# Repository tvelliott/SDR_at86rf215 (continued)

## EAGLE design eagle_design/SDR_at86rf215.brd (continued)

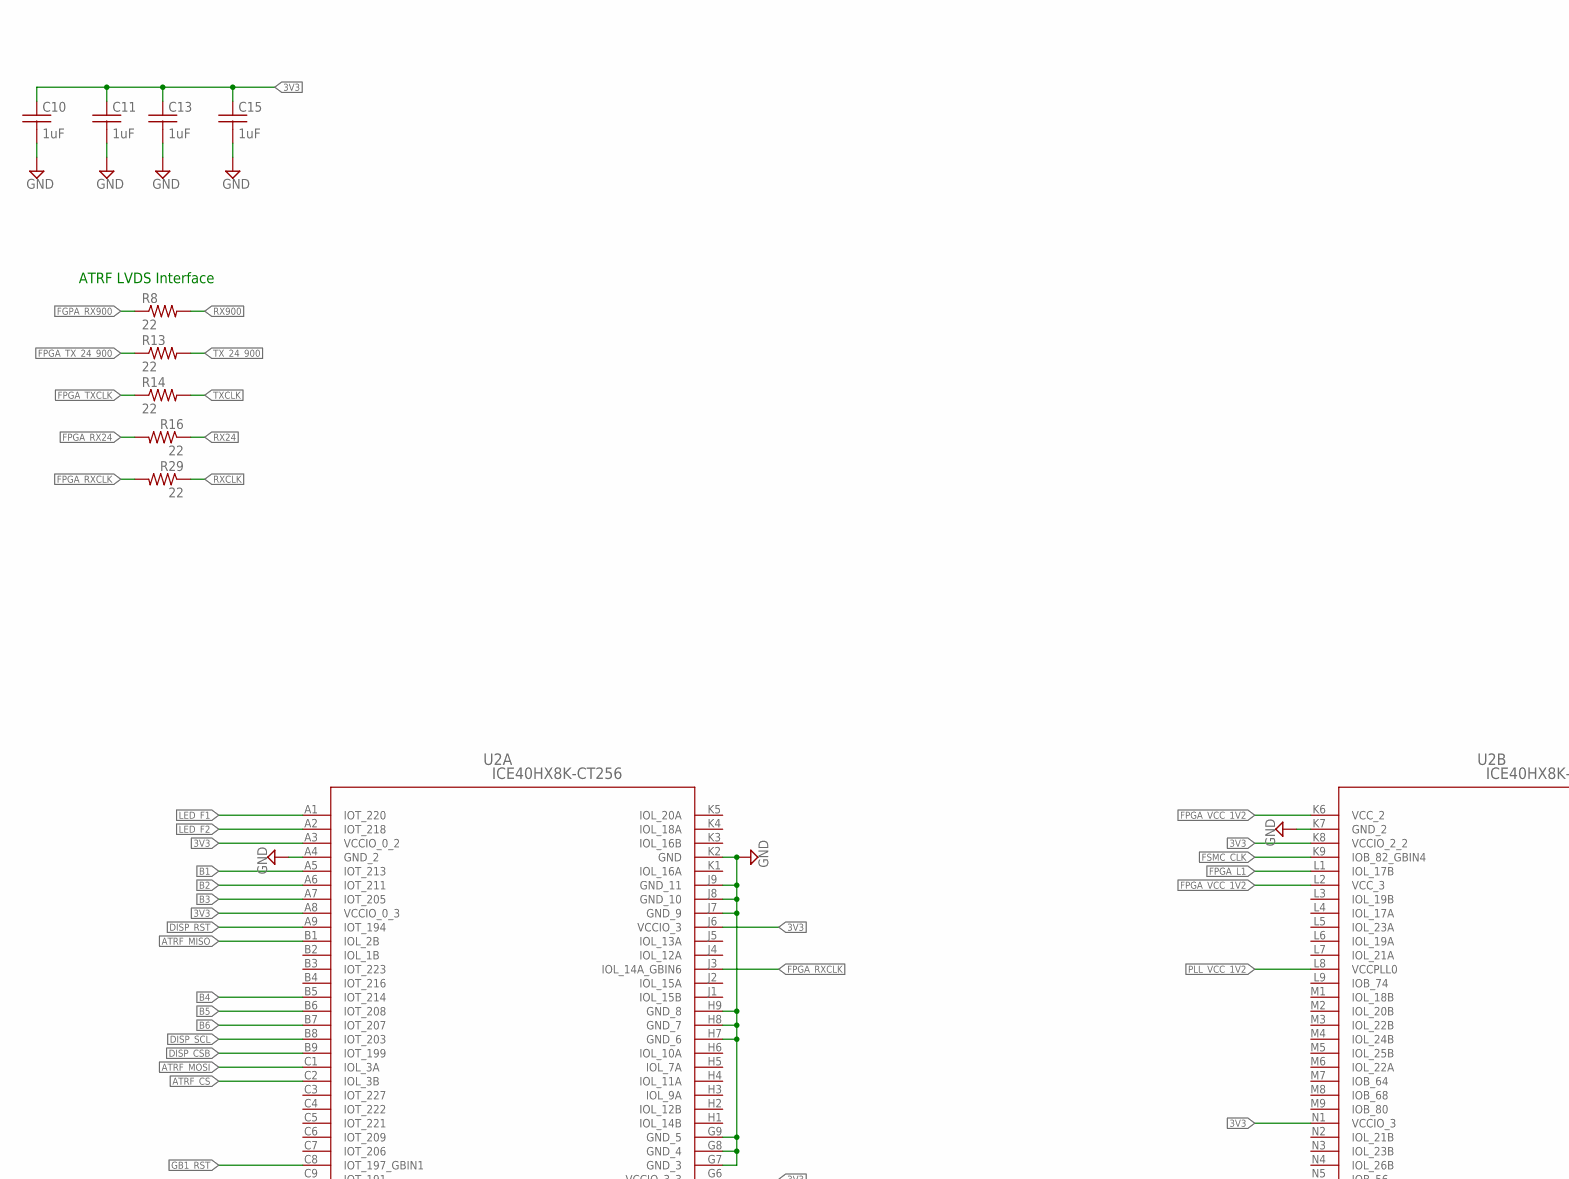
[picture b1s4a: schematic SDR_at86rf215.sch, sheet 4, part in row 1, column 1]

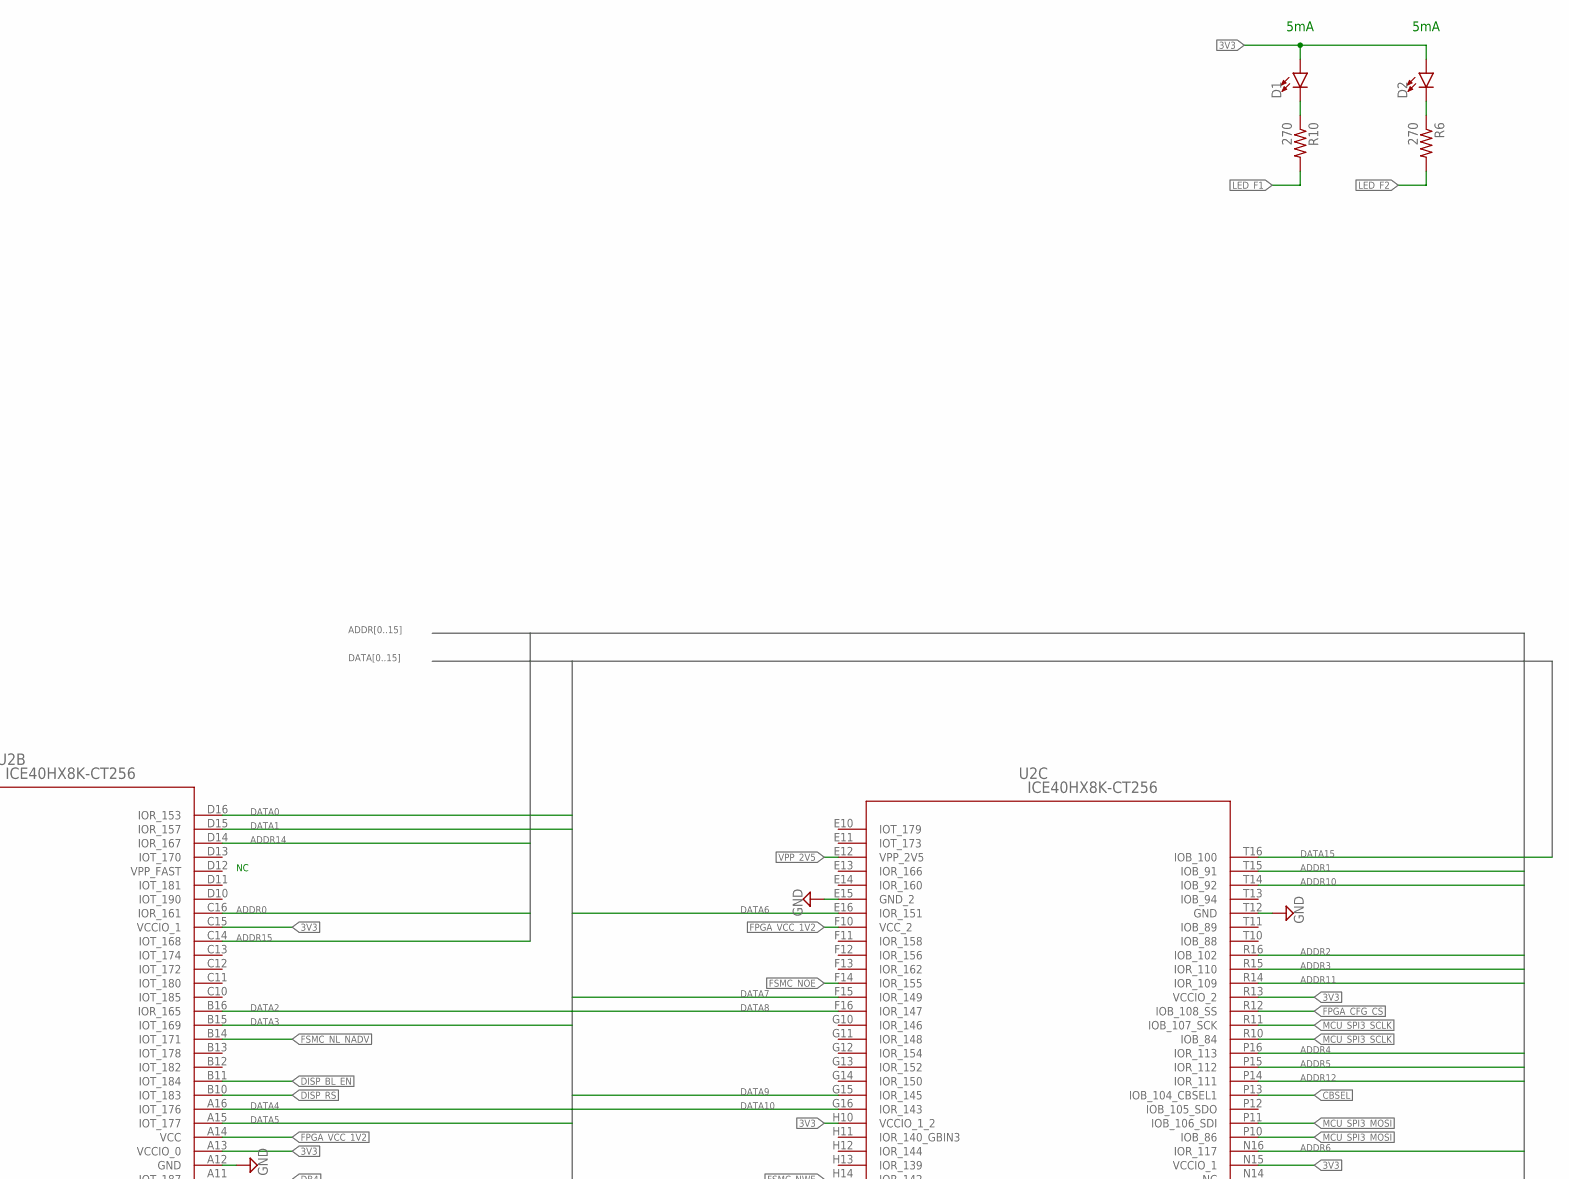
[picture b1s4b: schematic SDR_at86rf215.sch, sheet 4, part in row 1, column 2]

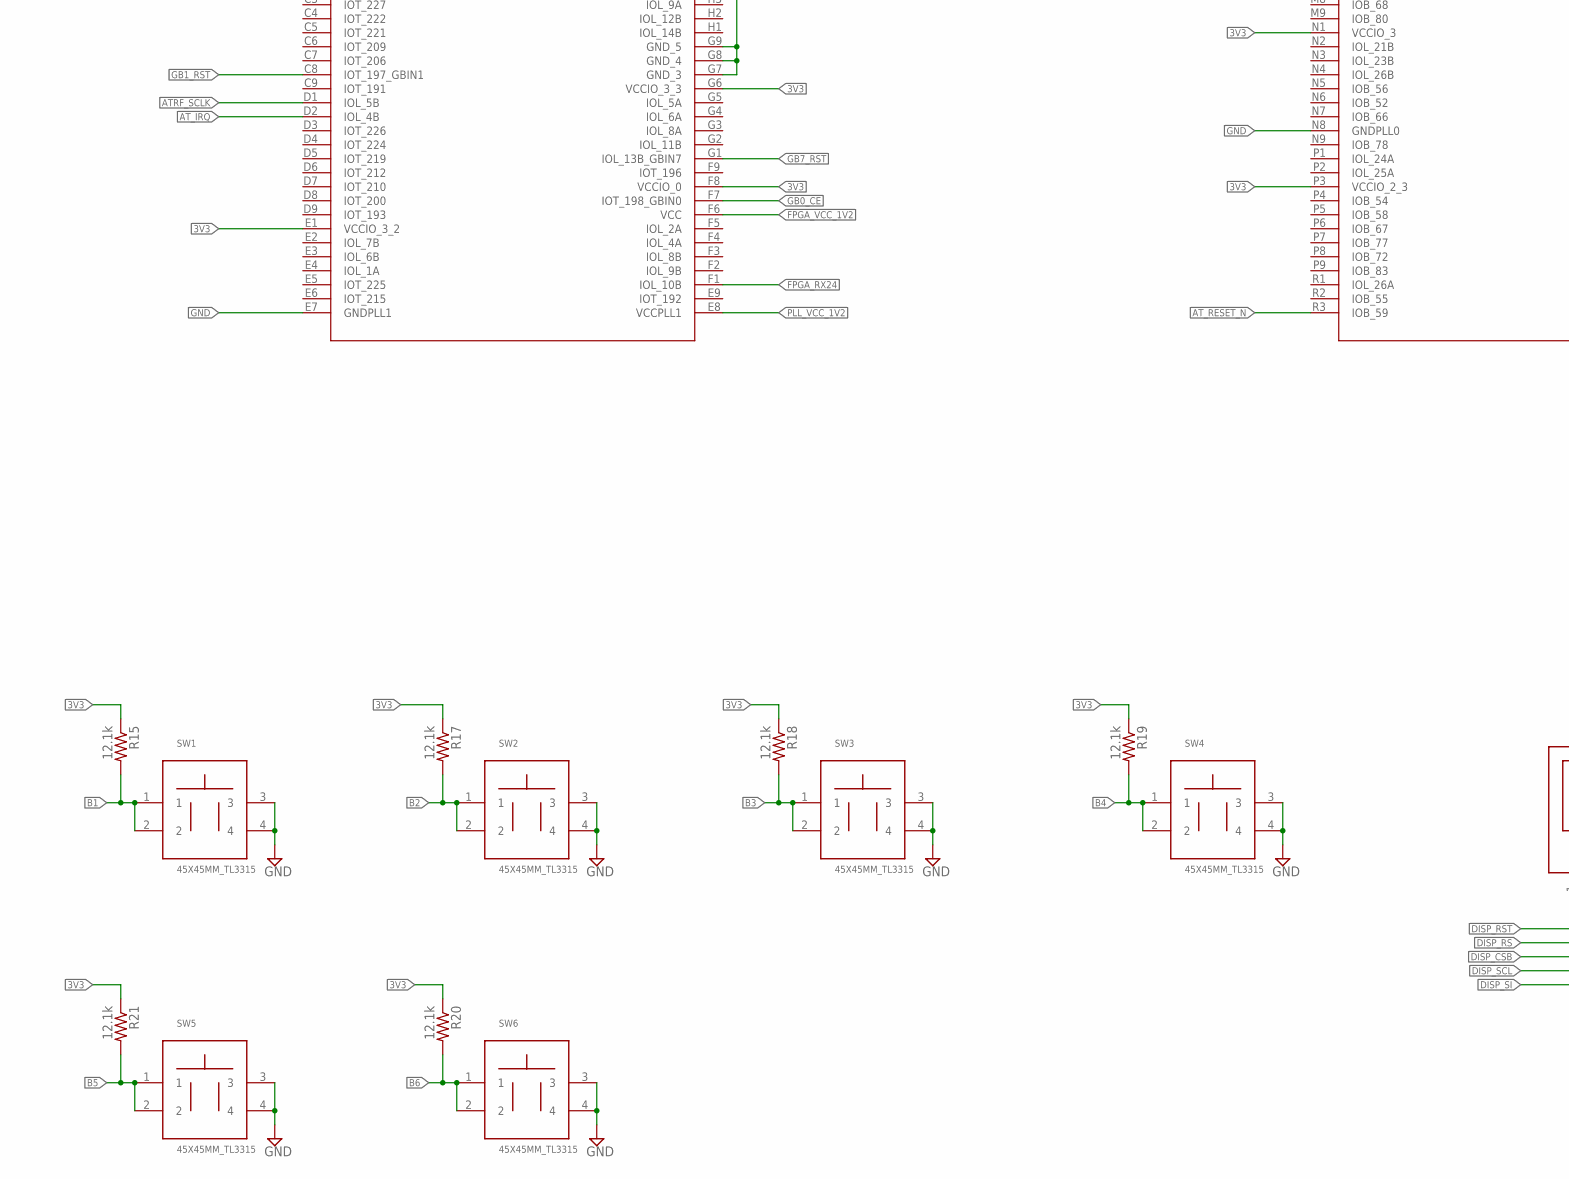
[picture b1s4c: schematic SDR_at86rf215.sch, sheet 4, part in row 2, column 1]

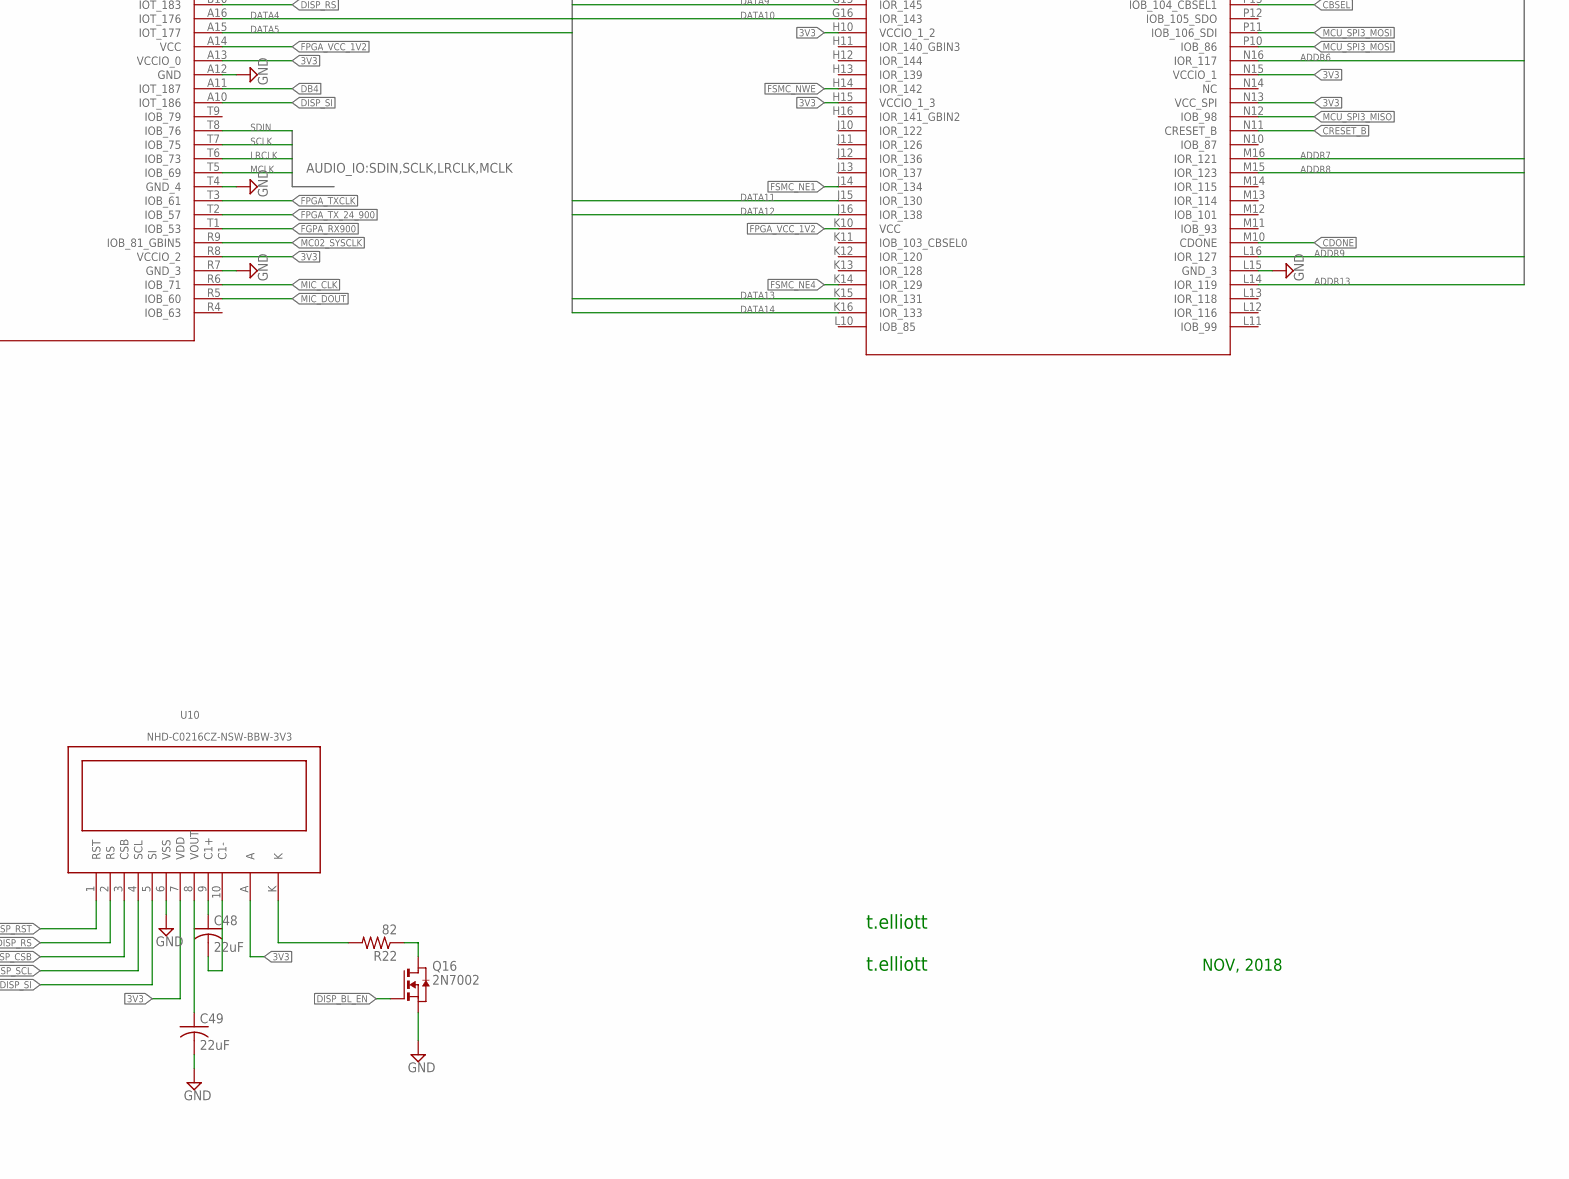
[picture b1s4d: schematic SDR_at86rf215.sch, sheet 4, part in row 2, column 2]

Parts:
C10, C11, C13, C15: 1uF; C0603
C48, C49: 22uF; 1210K
D1, D2: LED1206; LED-1206
Q16: 2N7002; SOT23_2N7002_PACKAGE
R6, R10: 270; R0603
R8, R13, R14, R16, R29: 22; R0603_COMPACT
R15, R17, R18, R19, R20, R21: 12.1k; R0603
R22: 82; R1206
SW1, SW2, SW3, SW4, SW5, SW6: 45X45MM_TL3315; PBUT_SW_TACTILE_4_5MMX4_5MM
U2: ICE40HX8K-CT256; CABGA256
U10: NHD-C0216CZ-NSW-BBW-3V3

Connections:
3V3: C10.1, C11.1, C13.1, C15.1, D1.A, D2.A, R15.1, R17.1, R18.1, R19.1, R20.1, R21.1, U2.A3 (VCCIO_0_2), U2.A8 (VCCIO_0_3), U2.A13 (VCCIO_0), U2.C15 (VCCIO_1), U2.E1 (VCCIO_3_2), U2.F8 (VCCIO_0), U2.G6 (VCCIO_3_3), U2.H10 (VCCIO_1_2), U2.H15 (VCCIO_1_3), U2.J6 (VCCIO_3), U2.K8 (VCCIO_2_2), U2.N1 (VCCIO_3), U2.N13 (VCC_SPI), U2.N15 (VCCIO_1), U2.P3 (VCCIO_2_3), U2.R8 (VCCIO_2), U2.R13 (VCCIO_2), U10.7 (VDD), U10.A; also elsewhere on the board
ADDR0: U2.C16 (IOR_161); also elsewhere on the board
ADDR1: U2.T15 (IOB_91); also elsewhere on the board
ADDR2: U2.R16 (IOB_102); also elsewhere on the board
ADDR3: U2.R15 (IOR_110); also elsewhere on the board
ADDR4: U2.P16 (IOR_113); also elsewhere on the board
ADDR5: U2.P15 (IOR_112); also elsewhere on the board
ADDR6: U2.N16 (IOR_117); also elsewhere on the board
ADDR7: U2.M16 (IOR_121); also elsewhere on the board
ADDR8: U2.M15 (IOR_123); also elsewhere on the board
ADDR9: U2.L16 (IOR_127); also elsewhere on the board
ADDR10: U2.T14 (IOB_92); also elsewhere on the board
ADDR11: U2.R14 (IOR_109); also elsewhere on the board
ADDR12: U2.P14 (IOR_111); also elsewhere on the board
ADDR13: U2.L14 (IOR_119); also elsewhere on the board
ADDR14: U2.D14 (IOR_167); also elsewhere on the board
ADDR15: U2.C14 (IOT_168); also elsewhere on the board
ATRF_CS: U2.C2 (IOL_3B); also elsewhere on the board
ATRF_MISO: U2.B1 (IOL_2B); also elsewhere on the board
ATRF_MOSI: U2.C1 (IOL_3A); also elsewhere on the board
ATRF_SCLK: U2.D1 (IOL_5B); also elsewhere on the board
AT_IRQ: U2.D2 (IOL_4B); also elsewhere on the board
AT_RESET_N: U2.R3 (IOB_59); also elsewhere on the board
B1: R15.2, SW1.1, SW1.2, U2.A5 (IOT_213)
B2: R17.2, SW2.1, SW2.2, U2.A6 (IOT_211)
B3: R18.2, SW3.1, SW3.2, U2.A7 (IOT_205)
B4: R19.2, SW4.1, SW4.2, U2.B5 (IOT_214)
B5: R21.2, SW5.1, SW5.2, U2.B6 (IOT_208)
B6: R20.2, SW6.1, SW6.2, U2.B7 (IOT_207)
CBSEL: U2.P13 (IOB_104_CBSEL1); also elsewhere on the board
CDONE: U2.M10 (CDONE); also elsewhere on the board
CRESET_B: U2.N11 (CRESET_B); also elsewhere on the board
DATA0: U2.D16 (IOR_153); also elsewhere on the board
DATA1: U2.D15 (IOR_157); also elsewhere on the board
DATA2: U2.B16 (IOR_165); also elsewhere on the board
DATA3: U2.B15 (IOT_169); also elsewhere on the board
DATA4: U2.A16 (IOT_176); also elsewhere on the board
DATA5: U2.A15 (IOT_177); also elsewhere on the board
DATA6: U2.E16 (IOR_151); also elsewhere on the board
DATA7: U2.F15 (IOR_149); also elsewhere on the board
DATA8: U2.F16 (IOR_147); also elsewhere on the board
DATA9: U2.G15 (IOR_145); also elsewhere on the board
DATA10: U2.G16 (IOR_143); also elsewhere on the board
DATA11: U2.J15 (IOR_130); also elsewhere on the board
DATA12: U2.J16 (IOR_138); also elsewhere on the board
DATA13: U2.K15 (IOR_131); also elsewhere on the board
DATA14: U2.K16 (IOR_133); also elsewhere on the board
DATA15: U2.T16 (IOB_100); also elsewhere on the board
DB4: U2.A11 (IOT_187)
DISP_BL_EN: Q16.1 (G), U2.B11 (IOT_184)
DISP_CSB: U2.B9 (IOT_199), U10.3 (CSB)
DISP_RS: U2.B10 (IOT_183), U10.2 (RS)
DISP_RST: U2.A9 (IOT_194), U10.1 (RST)
DISP_SCL: U2.B8 (IOT_203), U10.4 (SCL)
DISP_SI: U2.A10 (IOT_186), U10.5 (SI)
FGPA_RX900: R8.1, U2.T1 (IOB_53)
FPGA_CFG_CS: U2.R12 (IOB_108_SS); also elsewhere on the board
FPGA_L1: U2.L1 (IOL_17B)
FPGA_RX24: R16.2, U2.F1 (IOL_10B)
FPGA_RXCLK: R29.2, U2.J3 (IOL_14A_GBIN6)
FPGA_TXCLK: R14.1, U2.T3 (IOB_61)
FPGA_TX_24_900: R13.1, U2.T2 (IOB_57)
FPGA_VCC_1V2: U2.A14 (VCC), U2.F6 (VCC), U2.F10 (VCC_2), U2.K6 (VCC_2), U2.K10 (VCC), U2.L2 (VCC_3); also elsewhere on the board
FSMC_CLK: U2.K9 (IOB_82_GBIN4); also elsewhere on the board
FSMC_NE1: U2.J14 (IOR_134); also elsewhere on the board
FSMC_NE4: U2.K14 (IOR_129); also elsewhere on the board
FSMC_NL_NADV: U2.B14 (IOT_171); also elsewhere on the board
FSMC_NOE: U2.F14 (IOR_155); also elsewhere on the board
FSMC_NWE: U2.H14 (IOR_142); also elsewhere on the board
GB0_CE: U2.F7 (IOT_198_GBIN0)
GB1_RST: U2.C8 (IOT_197_GBIN1)
GB7_RST: U2.G1 (IOL_13B_GBIN7)
GND: C10.2, C11.2, C13.2, C15.2, C49.C, Q16.2 (S), SW1.3, SW1.4, SW2.3, SW2.4, SW3.3, SW3.4, SW4.3, SW4.4, SW5.3, SW5.4, SW6.3, SW6.4, U2.A4 (GND_2), U2.A12 (GND), U2.E7 (GNDPLL1), U2.E15 (GND_2), U2.G7 (GND_3), U2.G8 (GND_4), U2.G9 (GND_5), U2.H7 (GND_6), U2.H8 (GND_7), U2.H9 (GND_8), U2.J7 (GND_9), U2.J8 (GND_10), U2.J9 (GND_11), U2.K2 (GND), U2.K7 (GND_2), U2.L15 (GND_3), U2.N8 (GNDPLL0), U2.R7 (GND_3), U2.T4 (GND_4), U2.T12 (GND), U10.6 (VSS); also elsewhere on the board
LED_F1: R10.2, U2.A1 (IOT_220)
LED_F2: R6.2, U2.A2 (IOT_218)
LRCLK: U2.T6 (IOB_73); also elsewhere on the board
MC02_SYSCLK: U2.R9 (IOB_81_GBIN5); also elsewhere on the board
MCLK: U2.T5 (IOB_69); also elsewhere on the board
MCU_SPI3_MISO: U2.N12 (IOB_98); also elsewhere on the board
MCU_SPI3_MOSI: U2.P10 (IOB_86), U2.P11 (IOB_106_SDI); also elsewhere on the board
MCU_SPI3_SCLK: U2.R10 (IOB_84), U2.R11 (IOB_107_SCK); also elsewhere on the board
MIC_CLK: U2.R6 (IOB_71); also elsewhere on the board
MIC_DOUT: U2.R5 (IOB_60); also elsewhere on the board
unnamed: D1.C, R10.1
unnamed: D2.C, R6.1
unnamed: C48.A, U10.9 (C1+)
unnamed: C48.C, U10.10 (C1-)
unnamed: C49.A, U10.8 (VOUT)
unnamed: Q16.3 (D), R22.1
unnamed: R22.2, U10.K
PLL_VCC_1V2: U2.E8 (VCCPLL1), U2.L8 (VCCPLL0); also elsewhere on the board
RX24: R16.1; also elsewhere on the board
RX900: R8.2; also elsewhere on the board
RXCLK: R29.1; also elsewhere on the board
SCLK: U2.T7 (IOB_75); also elsewhere on the board
SDIN: U2.T8 (IOB_76); also elsewhere on the board
TXCLK: R14.2; also elsewhere on the board
TX_24_900: R13.2; also elsewhere on the board
VPP_2V5: U2.E12 (VPP_2V5); also elsewhere on the board
VPP_FAST: U2.D12 (VPP_FAST)

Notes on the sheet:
5mA
t.elliott
ATRF LVDS Interface
NOV, 2018

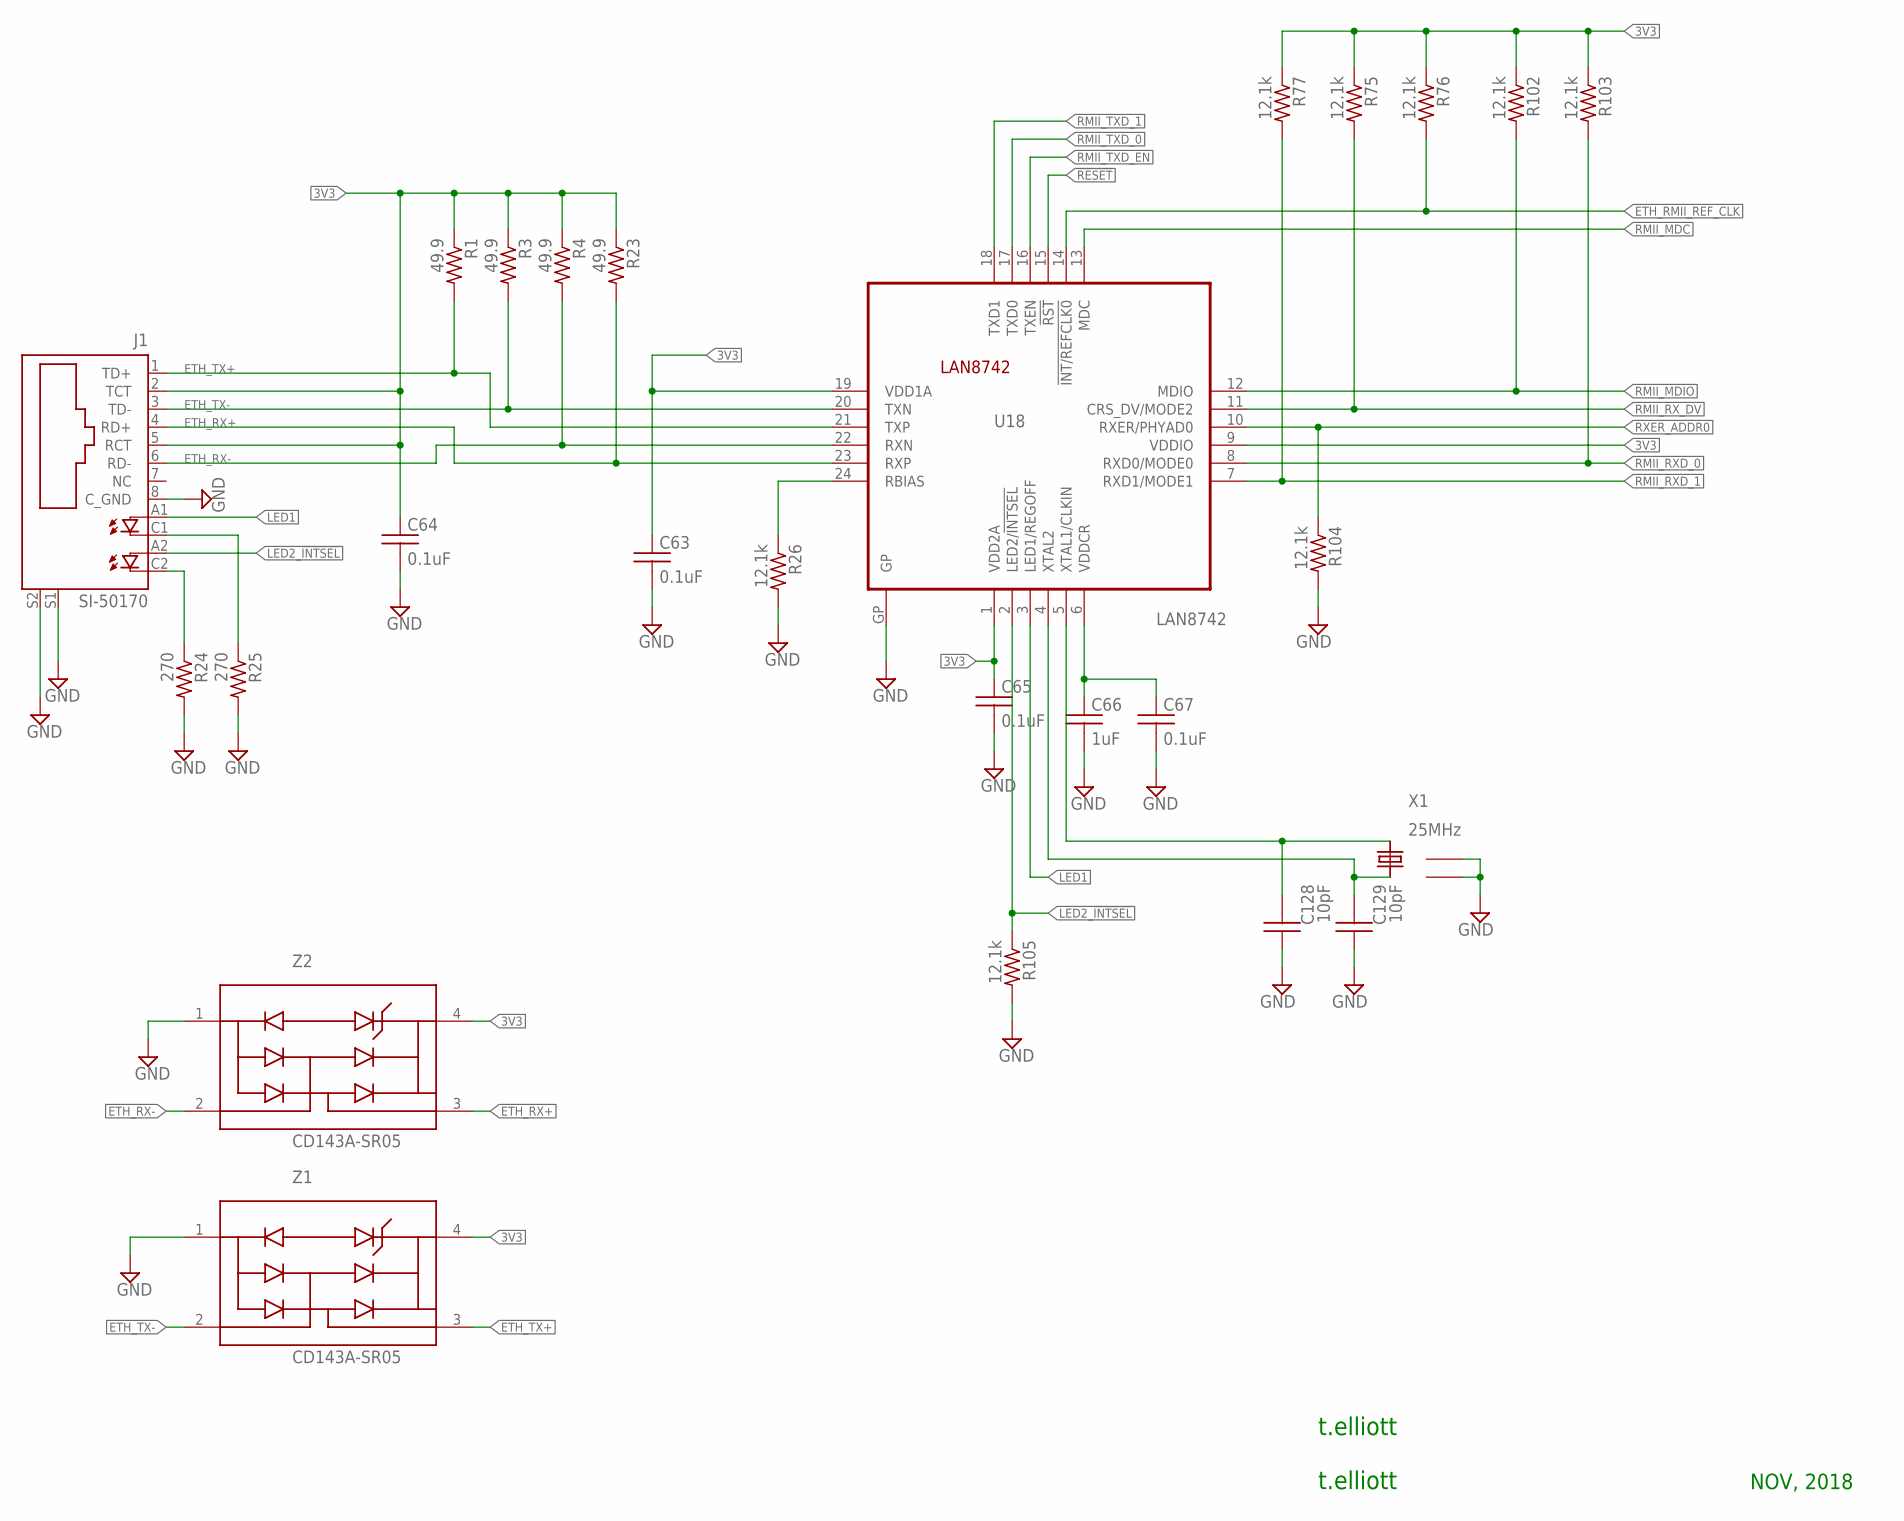
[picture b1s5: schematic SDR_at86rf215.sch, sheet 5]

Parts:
C63, C64, C65, C67: 0.1uF; C0603
C66: 1uF; C0603
C128, C129: 10pF; C0402
J1: SI-50170
R1, R3, R4, R23: 49.9; R0603
R24, R25: 270; R0603
R26, R75, R76, R77, R102, R103, R104, R105: 12.1k; R0603
U18: LAN8742; QFN-24
X1: 25MHz; ECS-250-20-30B-DU_CRYSTAL
Z1, Z2: CD143A-SR05; SR2.8.TCT_1PRIMARY

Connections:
3V3: C63.1, C64.1, C65.1, J1.2 (TCT), J1.5 (RCT), R1.1, R3.1, R4.1, R23.1, R75.1, R76.1, R77.1, R102.1, R103.1, U18.1 (VDD2A), U18.9 (VDDIO), U18.19 (VDD1A), Z1.4 (REF), Z2.4 (REF); also elsewhere on the board
!RESET: U18.15 (!RST); also elsewhere on the board
ETH_RMII_REF_CLK: R76.2, U18.14 (!INT/REFCLK0); also elsewhere on the board
ETH_RX+: J1.4 (RD+), R23.2, U18.23 (RXP), Z2.3 (I/O)
ETH_RX-: J1.6 (RD-), R4.2, U18.22 (RXN), Z2.2 (I/O)
ETH_TX+: J1.1 (TD+), R1.2, U18.21 (TXP), Z1.3 (I/O)
ETH_TX-: J1.3 (TD-), R3.2, U18.20 (TXN), Z1.2 (I/O)
GND: C63.2, C64.2, C65.2, C66.2, C67.2, C128.1, C129.1, J1.8 (C_GND), J1.S1, J1.S2, R24.2, R25.2, R26.2, R104.2, R105.2, U18.GP, X1.GND@1 (1), X1.GND@2 (2), Z1.1 (GND), Z2.1 (GND); also elsewhere on the board
LED1: J1.A1 (A), U18.3 (LED1/REGOFF)
LED2_!INTSEL: J1.A2 (A1), R105.1, U18.2 (LED2/!INTSEL)
unnamed: R26.1, U18.24 (RBIAS)
unnamed: C66.1, C67.1, U18.6 (VDDCR)
unnamed: J1.C2 (C1), R24.1
unnamed: J1.C1 (C), R25.1
unnamed: C129.2, U18.4 (XTAL2), X1.3
unnamed: C128.2, U18.5 (XTAL1/CLKIN), X1.1
RMII_MDC: U18.13 (MDC); also elsewhere on the board
RMII_MDIO: R102.2, U18.12 (MDIO); also elsewhere on the board
RMII_RXD_0: R103.2, U18.8 (RXD0/MODE0); also elsewhere on the board
RMII_RXD_1: R77.2, U18.7 (RXD1/MODE1); also elsewhere on the board
RMII_RX_DV: R75.2, U18.11 (CRS_DV/MODE2); also elsewhere on the board
RMII_TXD_0: U18.17 (TXD0); also elsewhere on the board
RMII_TXD_1: U18.18 (TXD1); also elsewhere on the board
RMII_TXD_EN: U18.16 (TXEN); also elsewhere on the board
RXER_ADDR0: R104.1, U18.10 (RXER/PHYAD0)

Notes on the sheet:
t.elliott
NOV, 2018

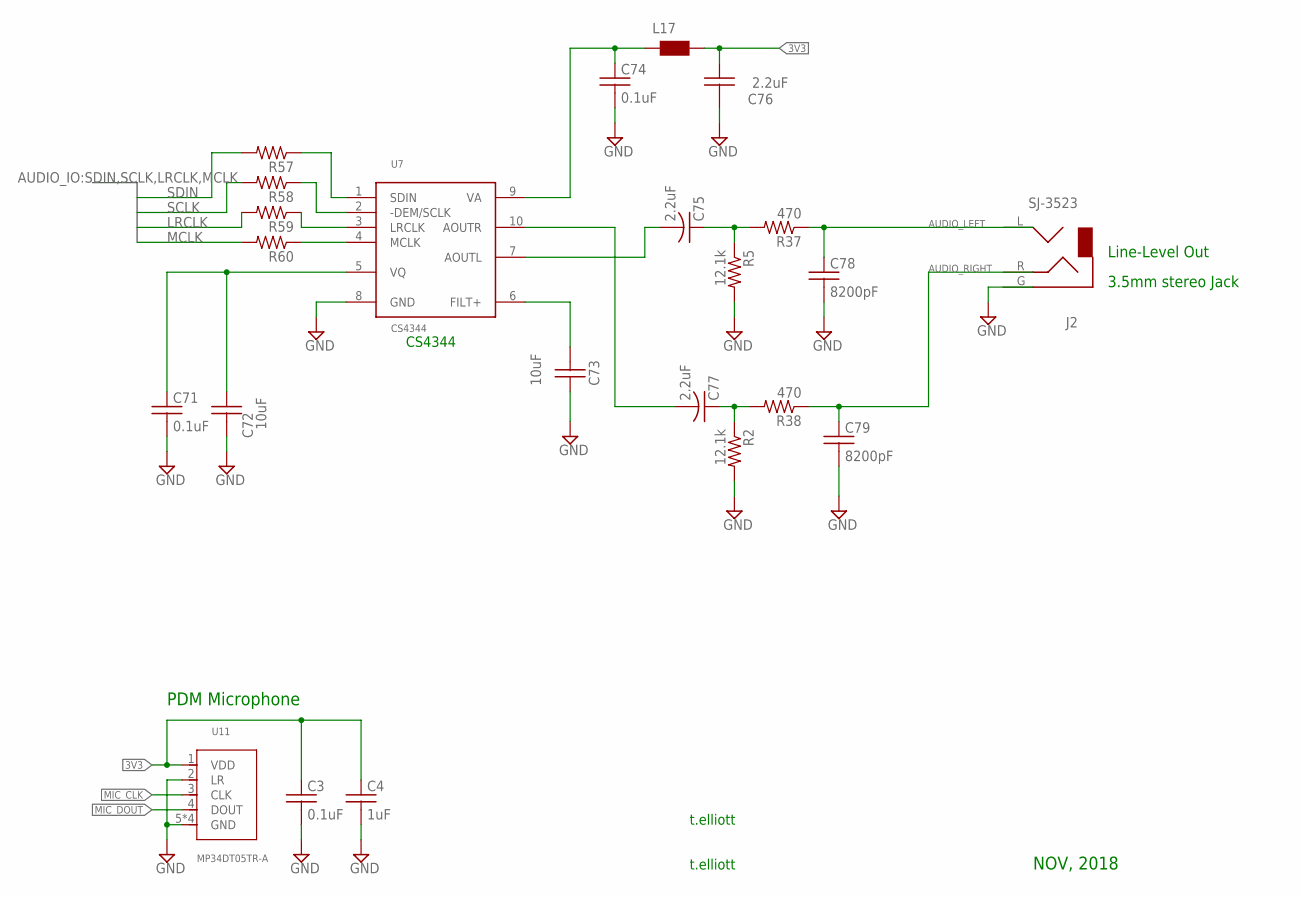
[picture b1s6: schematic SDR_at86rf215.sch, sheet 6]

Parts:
C3, C71, C74: 0.1uF; C0603
C4: 1uF; C0603
C72, C73: 10uF; C0805
C75, C76, C77: 2.2uF; C0805
C78, C79: 8200pF; C0603
J2: SJ-3523
L17: WE-CBF_0603; 0603
R2, R5: 12.1k; R0603
R37, R38, R57, R58, R59, R60: 470; R0402
U7: CS4344; MSOP10
U11: MP34DT05TR-A; HCLGA5P-3X4X1MM

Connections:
3V3: C3.1, C4.1, C76.1, L17.2, U11.1 (VDD); also elsewhere on the board
AUDIO_LEFT: C79.1, J2.R, R38.1
AUDIO_RIGHT: C78.1, J2.L, R37.1
GND: C3.2, C4.2, C71.2, C72.2, C73.1, C74.2, C76.2, C78.2, C79.2, J2.G, R2.2, R5.2, U7.8 (GND), U11.2 (LR), U11.5 (GND), U11.6 (GND), U11.7 (GND), U11.8 (GND); also elsewhere on the board
LRCLK: R59.2; also elsewhere on the board
MCLK: R60.2; also elsewhere on the board
MIC_CLK: U11.3 (CLK); also elsewhere on the board
MIC_DOUT: U11.4 (DOUT); also elsewhere on the board
unnamed: C77.2, U7.10 (AOUTR)
unnamed: R60.1, U7.4 (MCLK)
unnamed: R59.1, U7.3 (LRCLK)
unnamed: R58.1, U7.2 (-DEM/SCLK)
unnamed: R57.1, U7.1 (SDIN)
unnamed: C73.2, U7.6 (FILT+)
unnamed: C71.1, C72.1, U7.5 (VQ)
unnamed: C75.2, U7.7 (AOUTL)
unnamed: C75.1, R5.1, R37.2
unnamed: C77.1, R2.1, R38.2
unnamed: C74.1, L17.1, U7.9 (VA)
SCLK: R58.2; also elsewhere on the board
SDIN: R57.2; also elsewhere on the board

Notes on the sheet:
t.elliott
CS4344
Line-Level Out
3.5mm stereo Jack
PDM Microphone
NOV, 2018

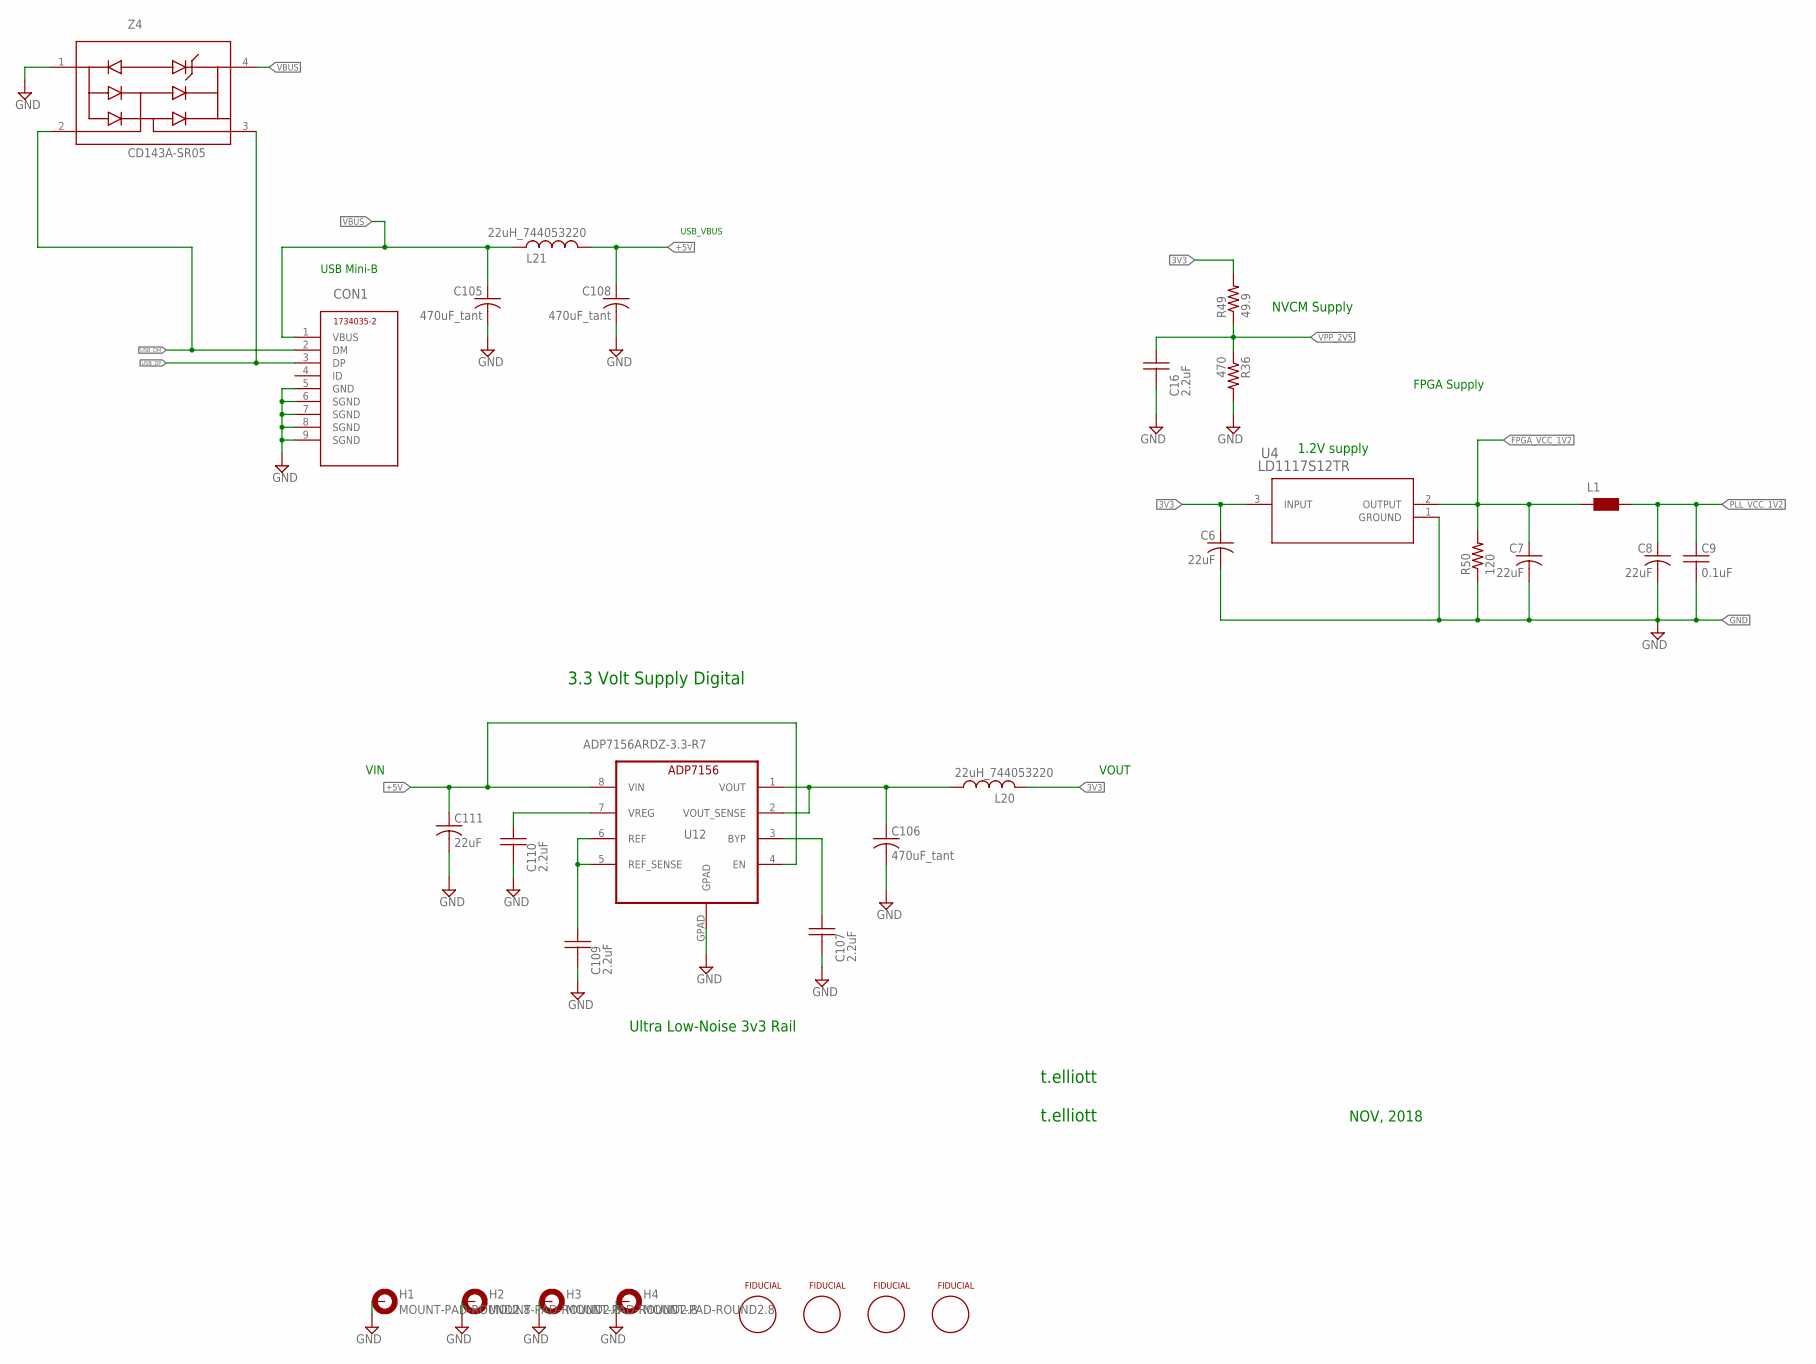
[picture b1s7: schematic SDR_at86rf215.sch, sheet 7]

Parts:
C6, C7, C8, C111: 22uF; 1210K
C9: 0.1uF; C0603
C16, C107, C109, C110: 2.2uF; C0805
C105, C106, C108: 470uF_tant; 1210K
CON1: 1734035-2
FID1, FID2, FID3, FID4: FIDUCIALSMD; FIDUCIAL
H1, H2, H3, H4: MOUNT-PAD-ROUND2.8; 2,8-PAD
L1: WE-CBF_0603; 0603
L20, L21: 22uH_744053220; POWER-CHOKE_WE-TPC
R36: 470; R0402
R49: 49.9; R0603
R50: 120; R0603
U4: LD1117S12TR; SOT-223
U12: ADP7156ARDZ-3.3-R7; SO8
Z4: CD143A-SR05; SR2.8.TCT_1PRIMARY

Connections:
3V3: C6.A, L20.2, R49.2, U4.3 (INPUT); also elsewhere on the board
+5V: C108.A, C111.A, L21.1, U12.4 (EN), U12.8 (VIN); also elsewhere on the board
FPGA_VCC_1V2: C7.A, L1.1, R50.2, U4.2 (OUTPUT); also elsewhere on the board
GND: C6.C, C7.C, C8.C, C9.2, C16.2, C105.C, C106.C, C107.2, C108.C, C109.2, C110.2, C111.C, CON1.5 (GND), CON1.6 (SGND), CON1.7 (SGND), CON1.8 (SGND), CON1.9 (SGND), H1.B2,8, H2.B2,8, H3.B2,8, H4.B2,8, R36.2, R50.1, U4.1 (GROUND), U12.GPAD, Z4.1 (GND); also elsewhere on the board
unnamed: C106.A, L20.1, U12.1 (VOUT), U12.2 (VOUT_SENSE)
unnamed: C109.1, U12.5 (REF_SENSE), U12.6 (REF)
unnamed: C110.1, U12.7 (VREG)
unnamed: C107.1, U12.3 (BYP)
PLL_VCC_1V2: C8.A, C9.1, L1.2; also elsewhere on the board
USB_DM: CON1.2 (DM), Z4.2 (I/O); also elsewhere on the board
USB_DP: CON1.3 (DP), Z4.3 (I/O); also elsewhere on the board
VBUS: C105.A, CON1.1 (VBUS), L21.2, Z4.4 (REF)
VPP_2V5: C16.1, R36.1, R49.1; also elsewhere on the board

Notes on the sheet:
t.elliott
VIN
VOUT
3.3 Volt Supply Digital
USB Mini-B
USB_VBUS
1.2V supply
NVCM Supply
Ultra Low-Noise 3v3 Rail
FPGA Supply
NOV, 2018
